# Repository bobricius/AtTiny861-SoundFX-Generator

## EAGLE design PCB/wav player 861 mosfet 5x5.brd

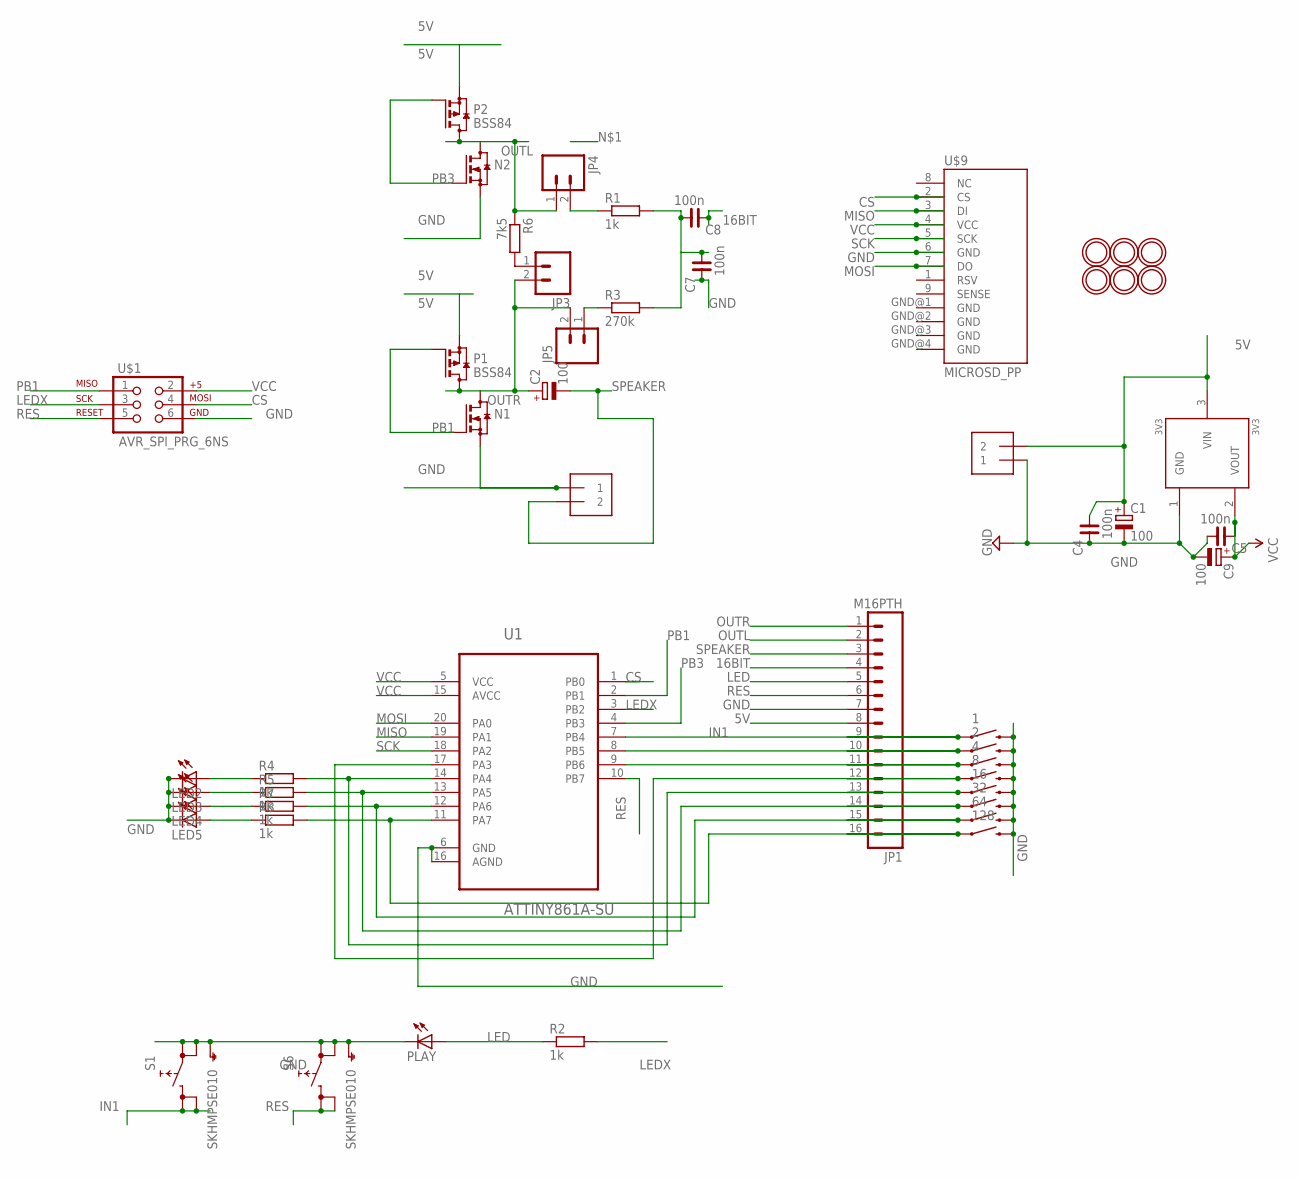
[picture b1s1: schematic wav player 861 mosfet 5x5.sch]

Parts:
1, 2, 4, 8, 16, 32, 64, 128: SWITCH-MOMENTARY-2-SMD-1101NE; TACTILE-SWITCH-1101NE
3V3: 3V3; SOT23
C1, C2, C9: 100; 153CLV-0605
C4, C5, C7, C8: 100n; C0603
J1, J2: 1X2-3.5MM
JP1: M16PTH; 1X16
JP3, JP4, JP5: M02PTH; 1X02
LED2, LED3, LED4, LED5: LED3MM
N1, N2: BSS123; SOT23
P1, P2: BSS84; SOT23
PLAY: LED3MM
R1, R2, R4, R5, R7, R8: 1k; R0603
R3: 270k; R0603
R6: 7k5; R0603
S1, S6: SKHMPSE010; SKHMPXE010
U1: ATTINY861A-SU; SOIC127P1032X265-20N
U$1: AVR_SPI_PRG_6NS; 2X3-NS
U$2, U$3, U$4, U$5, U$6, U$7: MOUNTINGHOLE2.0; MOUNTINGHOLE_2.0_PLATED
U$9: MICROSD_PP

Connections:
5V: 3V3.3 (VIN), C1.+, C4.1, J2.2, JP1.8, P1.2 (S), P2.2 (S)
16BIT: C8.2, JP1.4
CS: U1.1 (PB0), U$1.4, U$9.2 (CS)
GND: 1.P$2 (2), 2.P$2 (2), 3V3.1 (GND), 4.P$2 (2), 8.P$2 (2), 16.P$2 (2), 32.P$2 (2), 64.P$2 (2), 128.P$2 (2), C1.-, C4.2, C5.1, C7.2, C9.-, J1.1, J2.1, JP1.7, LED2.K (C), LED3.K (C), LED4.K (C), LED5.K (C), N1.2 (S), N2.2 (S), PLAY.K (C), S1.1 (1.1), S1.2 (1.2), S1.5 (SH), S6.1 (1.1), S6.2 (1.2), S6.5 (SH), U1.6 (GND), U1.16 (AGND), U$1.6, U$9.6 (GND)
IN1: 1.P$1 (1), JP1.9, S1.3 (2.1), S1.4 (2.2), U1.7 (PB4)
LED: JP1.5, PLAY.A, R2.1
LEDX: R2.2, U1.3 (PB2), U$1.3
MISO: U1.19 (PA1), U$9.3 (DI)
MOSI: U1.20 (PA0), U$9.7 (DO)
unnamed: JP3.1, R6.2
unnamed: C7.1, C8.1, R1.2, R3.2
unnamed: LED2.A, R4.1
unnamed: LED3.A, R5.1
unnamed: LED4.A, R7.1
unnamed: LED5.A, R8.1
unnamed: JP5.1, R3.1
unnamed: JP4.2, R1.1
unnamed: 2.P$1 (1), JP1.10, U1.8 (PB5)
unnamed: 4.P$1 (1), JP1.11, U1.9 (PB6)
unnamed: 8.P$1 (1), JP1.12, U1.17 (PA3)
unnamed: 16.P$1 (1), JP1.13, R4.2, U1.14 (PA4)
unnamed: 32.P$1 (1), JP1.14, R5.2, U1.13 (PA5)
unnamed: 64.P$1 (1), JP1.15, R7.2, U1.12 (PA6)
unnamed: 128.P$1 (1), JP1.16, R8.2, U1.11 (PA7)
OUTL: JP1.2, JP4.1, N2.3 (D), P2.3 (D), R6.1
OUTR: C2.+, JP1.1, JP3.2, JP5.2, N1.3 (D), P1.3 (D)
PB1: N1.1 (G), P1.1 (G), U1.2 (PB1), U$1.1
PB3: N2.1 (G), P2.1 (G), U1.4 (PB3)
RES: JP1.6, S6.3 (2.1), S6.4 (2.2), U1.10 (PB7), U$1.5
SCK: U1.18 (PA2), U$9.5 (SCK)
SPEAKER: C2.-, J1.2, JP1.3
VCC: 3V3.2 (VOUT), C5.2, C9.+, U1.5 (VCC), U1.15 (AVCC), U$1.2, U$9.4 (VCC)

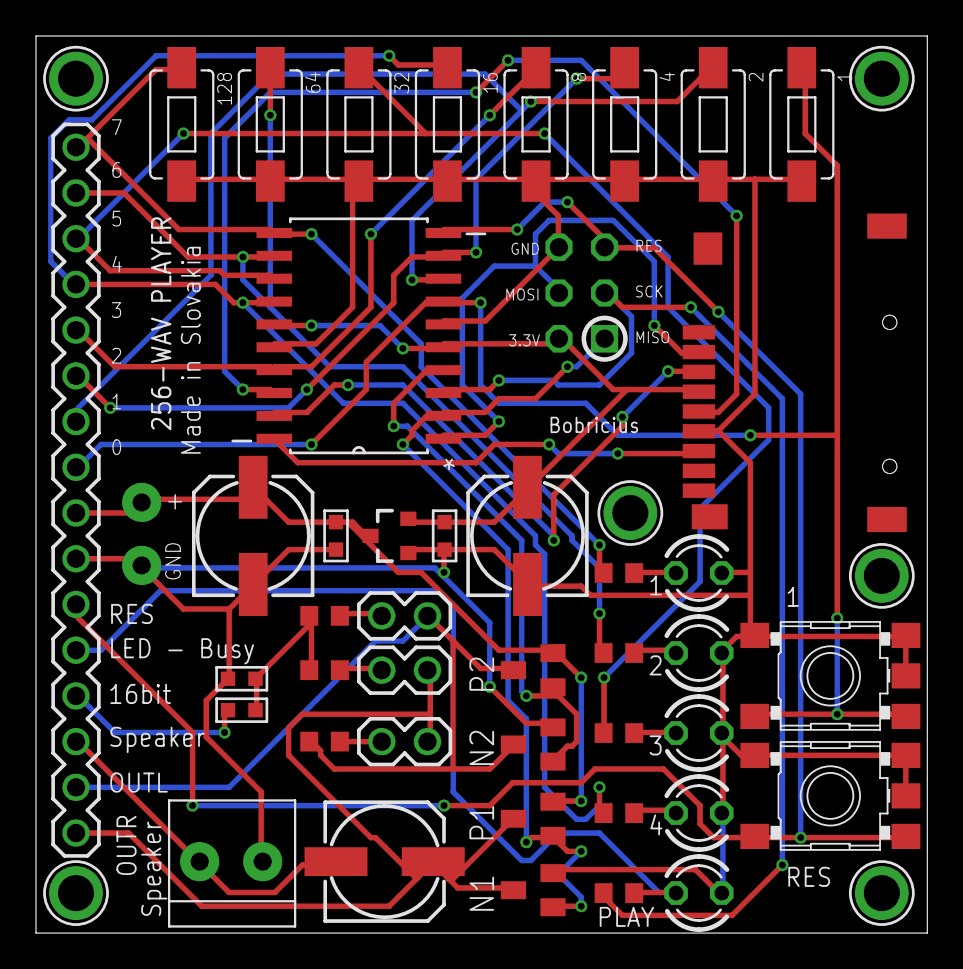
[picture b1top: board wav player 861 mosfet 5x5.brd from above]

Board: 2 copper layers, 49.5 x 49.8 mm, 50 parts (1 on the bottom side), 32 nets.

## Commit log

2014-11-12 :circus_tent: Added .gitattributes & .gitignore files
2014-11-12 first upload
